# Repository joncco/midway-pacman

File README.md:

This is a reproduction of the PAC-MAN Main Logic board used in Midway's Pac-Man arcade machine.

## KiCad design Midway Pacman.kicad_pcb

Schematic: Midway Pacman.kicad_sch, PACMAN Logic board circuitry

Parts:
C1: 0.01uF; C_Axial_L3.8mm_D2.6mm_P7.70mm_Horizontal
C2, C3: 470uF 10V ELECT.; CP_Axial_L25.0mm_D10.0mm_P30.00mm_Horizontal
C4: 100pF; C_Axial_D4.3mm_P5.00mm_Vertical
C5: 10uF TANT.; CP_Axial_L25.0mm_D10.0mm_P20.00mm_Horizontal
C6: 0.1uF CER.; C_Axial_L3.8mm_D2.6mm_P10.00mm_Horizontal
C7, C8: 10000uF 10V ELECT. AX.; CP_Axial_L25.0mm_D10.0mm_P48.76mm_Horizontal
C10: 10uF 18V TANT.; CP_Axial_L25.0mm_D10.0mm_P20.00mm_Horizontal
C12, C13, C14, C15, C16, C17, C18, C19, C20, C21, C22, C23, C24, C25, C26: .1uF CER.; C_Axial_D4.3mm_P7.6mm_P10.2mm_dual
C29: 2200uF 25V ELECT.; CP_Axial_L25.0mm_D10.0mm_P48.2mm_Horizontal
C34: 220pF; C_Axial_D4.3mm_P5.00mm_Vertical
C46: 0.1uF; C_Axial_L10.0mm_D4.5mm_P11.50mm_Horizontal
C47: 22pF CER; C_Axial_L10.0mm_D4.5mm_P11.50mm_Horizontal
C48: 4.7uF ELECT. 10v; CP_Axial_D4.3mm_P7.6mm_P18mm_dual
C49: 0.47uF TANT.; C_Oval_L4.6mm_W2.0mm_P2.80mm_MKS02_FKP02
C50: 0.0047uF 100V MYLAR; C_Oval_L4.6mm_W2.0mm_P2.50mm_MKS02_FKP02
C51: 330uF 10V ELECT.; CP_Axial_L25.0mm_D10.0mm_P35.5mm_Horizontal
CP1, CP2, CP3, CP4, CP5, CP6, CP7, CP9, CP10, CP11, CP13, CP14, CP15, CP16, CP17, CP18, CP19, CP20, CP21, CP22, CP23, CP24: 0.1uF; C_Axial_D4.3mm_P7.6mm_P10mm_dual
CP8, CP12, CP25: 0.1uF; C_Axial_D4.3mm_P7.6mm
D1, D2: 1N914B; D_DO-35_SOD27_P11.5mm_Horizontal
D3, D4, D6: 1N4004; D_DO-41_SOD81_P12.753mm_Horizontal
D7, D8: A15; D_DO-41_SOD81_P17.6mm_Horizontal
D9: 1N4735; D_DO-41_SOD81_P12.753mm_Horizontal
H1, H2, H3, H4: MountingHole; MountingHole_3mm
H5, H6, H7, H8, H9, H10: MountingHole; MountingHole_4mm
IR1: 78GU1C; TO-220-4_Vertical
J1: Factory TEST Connector; PAC-MAN_CPU_EDGE
J2: Conn_02x22_Namco_PM; PACMAN-EDGE-CONNECTOR
JP1, JP2, JP5, JP8: SolderJumper_2_Bridged; SolderJumper-2_P1.3mm_Bridged_RoundedPad1.0x1.5mm
JP3, JP4, JP6, JP7: SolderJumper_2_Open; SolderJumper-2_P1.3mm_Open_RoundedPad1.0x1.5mm
Q1: 2N3391A; TO-92
Q3: D40K1; TO-220-3_Vertical
Q6: D44VM4; TO-220-3_Horizontal_TabDown
R1, R5: 22K; R_Axial_DIN0207_L6.3mm_D2.5mm_P10mm_Horizontal
R2: 10K; R_Axial_DIN0207_L6.3mm_D2.5mm_P10mm_Horizontal
R3: 47K; R_Axial_DIN0207_L6.3mm_D2.5mm_P10mm_Horizontal
R4: 100K; R_Axial_DIN0207_L6.3mm_D2.5mm_P10mm_Horizontal
R6: 4.7K; R_Axial_DIN0207_L6.3mm_D2.5mm_P10mm_Horizontal
R7: 2.2K; R_Axial_DIN0207_L6.3mm_D2.5mm_P10mm_Horizontal
R8, R10, R11, R12, R14, R18, R19, R35, R54, R55, R57, R58, R59: 1K; R_Axial_DIN0207_L6.3mm_D2.5mm_P10mm_Horizontal
R9, R15, R17, R34: 470; R_Axial_DIN0207_L6.3mm_D2.5mm_P10mm_Horizontal
R13, R16, R20, R33, R37, R38, R39, R40, R41, R42, R43, R44, R45, R46, R47, R48, R49, R50, R51: 220; R_Axial_DIN0207_L6.3mm_D2.5mm_P10mm_Horizontal
R21, R22, R23: 330; R_Axial_DIN0207_L6.3mm_D2.5mm_P10mm_Horizontal
R28, R29: 10K; R_Axial_DIN0207_L6.3mm_D2.5mm_P11.5mm_Horizontal
R30, R31, R32: 1K; R_Axial_DIN0207_L6.3mm_D2.5mm_P11.5mm_Horizontal
R36: 100; R_Axial_DIN0207_L6.3mm_D2.5mm_P10mm_Horizontal
R52: 50R 5W; R_Axial_Power_L25.0mm_W9.0mm_P27.94mm
R53: 4R 10W; R_Axial_Power_L50.0mm_W9.0mm_P60.96mm
R56: 1K; R_Axial_DIN0207_L6.3mm_D2.5mm_P10.4mm_Horizontal
R91: 10K; Potentiometer_ACP_CA14-H4_Horizontal
R92, R93, R95: 100K; R_Axial_DIN0207_L6.3mm_D2.5mm_P11.5mm_Horizontal
R94: 2K; R_Axial_DIN0207_L6.3mm_D2.5mm_P11.5mm_Horizontal
R96: 22K; R_Axial_DIN0207_L6.3mm_D2.5mm_P11.5mm_Horizontal
RM1, RM2, RM5: 1K x 5p; R_Array_SIP6
RM3, RM4, RM6, RM7, RM8: 1K x 8 OR 1K x 9; R_Array_SIP10
SW1: SW_Push; SW_Push_2P1T_Toggle_CK_PVA1xxH1xxxxxxV2
UA1: 27LS00; DIP-16_W7.62mm_square; not fitted
UA2: 8125; DIP-16_W7.62mm_square
UA3: 74LS158; DIP-16_W7.62mm_square
UA4: 5623; DIP-16_W7.62mm_square
UA5: 74LS157; DIP-16_W7.62mm_square
UA8: 74LS107; DIP-14_W7.62mm_square
UA11: LM1877; DIP-14_W7.62mm_LongPads
UB1: 27LS00; DIP-16_W7.62mm_square; not fitted
UB2: 8125; DIP-16_W7.62mm_square
UB3: 74LS157; DIP-16_W7.62mm_square
UB4: 74LS377; DIP-20_W7.62mm_square
UB5: 74LS194; DIP-16_W7.62mm_square
UB6: Z80CPU; DIP-40_W15.24mm
UB8: 74LS368; DIP-16_W7.62mm_square
UC1: 27LS00; DIP-16_W7.62mm_square; not fitted
UC2: 8125; DIP-16_W7.62mm_square
UC3: 74LS375; DIP-16_W7.62mm_square; not fitted
UC4: 74LS00; DIP-14_W7.62mm_square
UC5: 74LS194; DIP-16_W7.62mm_square
UC8: 74LS74; DIP-14_W7.62mm_square
UC9: 74LS161; DIP-16_W7.62mm_square
UD1: 27LS00; DIP-16_W7.62mm_square; not fitted
UD2: 8125; DIP-16_W7.62mm_square
UD3: 74LS75; DIP-16_W7.62mm_square
UD4: 74LS273; DIP-20_W7.62mm_square
UD6: 285; DIP-28_W15.24mm_square
UD8: 74LS367; DIP-16_W7.62mm_square
UD9: 8 POS DIP SW; DIP-16_W7.62mm_square
UE1, UE2: 74LS161/3; DIP-16_W7.62mm_square
UE3: 74LS20; DIP-14_W7.62mm_square
UE4: 74LS157; DIP-16_W7.62mm_square
UE5: 2716; DIP-24_W15.24mm
UE6: ROM; DIP-24_W15.24mm
UE8: 74LS367; DIP-16_W7.62mm_square
UF1, UF2: 74LS283; DIP-16_W7.62mm_square
UF3: 74LS89; DIP-16_W7.62mm_square
UF4: 74LS86; DIP-14_W7.62mm_square
UF5: 2716; DIP-24_W15.24mm
UF6: ROM; DIP-24_W15.24mm
UF7: 7603; DIP-16_W7.62mm_square
UF8: 74LS367; DIP-16_W7.62mm_square
UH1: 74LS174; DIP-16_W7.62mm_square
UH2: 74LS86; DIP-14_W7.62mm_square
UH3: 74LS89; DIP-16_W7.62mm_square
UH4, UH41: 8T245; DIP-20_W7.62mm_square
UH5: 2716; DIP-24_W15.24mm; not fitted
UH6: ROM; DIP-24_W15.24mm
UH7: 74LS08; DIP-14_W7.62mm_square
UH8: 74LS367; DIP-16_W7.62mm_square
UJ5: 2716; DIP-24_W15.24mm; not fitted
UJ6: ROM; DIP-24_W15.24mm
UJ7: 74LS138; DIP-16_W7.62mm_square
UK1: 74LS283; DIP-16_W7.62mm_square
UK2: 74LS89; DIP-16_W7.62mm_square
UK3: 74LS158; DIP-16_W7.62mm_square
UK4: 2114-2; DIP-18_W7.62mm_square
UK6: ROM; DIP-24_W15.24mm; not fitted
UK7: 4099; DIP-16_W7.62mm_square
UK8: 74LS259; DIP-16_W7.62mm_square
UL1: 74LS174; DIP-16_W7.62mm_square
UL2: 74LS89; DIP-16_W7.62mm_square
UL3: 74LS157; DIP-16_W7.62mm_square
UL4: 2114-2; DIP-18_W7.62mm_square
UL5: 74LS139; DIP-16_W7.62mm_square
UL7: 74LS02; DIP-14_W7.62mm_square
UM1: MB7052; DIP-16_W7.62mm_square
UM2: 74LS273; DIP-20_W7.62mm_square
UM3: MB7057; DIP-16_W7.62mm_square
UM4: 2114-2; DIP-18_W7.62mm_square
UM5: 74LS74; DIP-14_W7.62mm_square
UM6: ROM; DIP-24_W15.24mm; not fitted
UM7: 74LS139; DIP-16_W7.62mm_square
UN1: 4066; DIP-14_W7.62mm_square
UN3: 74LS74; DIP-14_W7.62mm_square
UN4: 2114-2; DIP-18_W7.62mm_square
UN5: 74LS08; DIP-14_W7.62mm_square
UN6: ROM; DIP-24_W15.24mm; not fitted
UN7: 74LS42; DIP-16_W7.62mm_square
UP2: 74LS02; DIP-14_W7.62mm_square
UP3: 74LS10; DIP-14_W7.62mm_square
UP4: 2114-2; DIP-18_W7.62mm_square
UP6: ROM; DIP-24_W15.24mm; not fitted
UP7: DIP_16_Breadboard; DIP-16_W7.62mm_bread_square; not fitted
UR1, UR7: DIP_16_Breadboard; DIP-16_W7.62mm_bread_square; not fitted
UR2, UR3: 74LS161/3; DIP-16_W7.62mm_square
UR4: 2114-2; DIP-18_W7.62mm_square
UR6: 74LS367; DIP-16_W7.62mm_square
US1, US4, US7: DIP_16_Breadboard; DIP-16_W7.62mm_bread_square; not fitted
US2, US3: 74LS161/3; DIP-16_W7.62mm_square
US5: 284; DIP-28_W15.24mm_square
US6: 74LS367; DIP-16_W7.62mm_square
X0: 18.432 MHz; Crystal_HC18-U_Horizontal_1EP_style1

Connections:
3: D8.2 (A), J2.3, J2.C (Pin_25)
4: D7.2 (A), J2.4, J2.D (Pin_26)
5: C7.1, C8.1, C10.1, D6.1 (K), D7.1 (K), D8.1 (K), J2.5, J2.E (Pin_27), Q6.2 (C), R53.2
6: J1.35, J2.6, UB6.26 (~RESET), UK8.15 (Clr), UL7.13
7: D6.2 (A), J2.7, Q3.3 (C)
8: J2.8, R51.1, RM8.3 (R2)
9: J2.9, R49.1, RM8.5 (R4)
10: J2.10, R43.1, RM7.3 (R2)
11: J2.11, R48.1, RM8.6 (R5)
12: J2.12, R41.1, RM7.5 (R4)
13: J2.13, R40.1, RM7.6 (R5)
14: J2.14, R45.1, RM8.9 (R8)
16: J2.16, R13.1, R14.1, R15.1
17: J2.17, R36.1
19: D3.2 (A), J2.19, J2.W (Pin_41)
20: D4.2 (A), J2.20, J2.X (Pin_42)
+16V: C29.1, C49.1, D3.1 (K), D4.1 (K), R52.2, UA11.14 (V+)
/1H: UB8.4, UC8.5 (Q), UD6.2 (1H), UH7.1, UM3.5 (A0), UN5.9, UP3.3, UR3.7, UR3.10 (T)
/1V: UF1.5 (A1), UM5.9 (Q), UR2.7, UR2.10 (T)
/2H: UD6.3 (2H), UF4.10, UH7.2, UL5.2 (A0), UM3.6 (A1), UN5.5, UN5.10, UP3.4, UR3.14 (Q0), UR6.1 (OEa), UR6.15 (OEb), US5.1 (2H), US6.1 (OEa), US6.15 (OEb)
/2V: UF1.3 (A2), UR2.14 (Q0)
/4H: UD4.11 (Cp), UF4.4, UH1.9 (Cp), UL3.13 (I1d), UM3.7 (A2), UP3.5, UR3.13 (Q1), US5.2 (4H)
/4V: UF1.14 (A3), UR2.13 (Q1)
/6M*: UB8.3, UC3.4 (E01), UC3.12 (E23), UD3.4 (E23), UD3.13 (E01), UD6.1 (6M*), UF4.12
/6_MHZ: UA1.12 (WE), UA2.14 (WE), UB1.12 (WE), UB2.14 (WE), UB4.11 (CP), UB5.11 (Cp), UB8.13, UC1.12 (WE), UC2.14 (WE), UC5.11 (Cp), UC8.3 (C), UD1.12 (WE), UD2.14 (WE), UE1.2 (CK), UE2.2 (CK), UR3.2 (CK), US3.2 (CK)
/8H: UE4.13 (I1d), UL3.10 (I1c), UM3.4 (A3), UP2.5, UR3.12 (Q2), US5.3 (8H)
/8V: UF1.12 (A4), UR2.12 (Q2), US5.9 (8V)
/16H: UL3.6 (I1b), UM3.3 (A4), UN3.3 (C), UN3.11 (C), UR3.11 (Q3), US5.4 (16H)
/16V: UF2.5 (A1), UM5.3 (C), UR2.11 (Q3), US5.10 (16V)
/32H: UL3.3 (I1a), UM3.2 (A5), UP3.1, US3.14 (Q0), US5.5 (32H)
/32V: UF2.3 (A2), UP3.11, US2.14 (Q0), US5.11 (32V)
/64H: UN3.12 (D), UP3.2, UP3.13, US3.13 (Q1), US5.6 (64H)
/64V: UF2.14 (A3), UP3.10, US2.13 (Q1), US5.12 (64V)
/128H: US3.12 (Q2), US5.7 (128H)
/128V: UF2.12 (A4), UP3.9, US2.12 (Q2), US5.13 (128V)
/256H: UN3.1 (~R), UN5.1, UP2.1
/A0: J1.27, UB6.30 (A0), UE6.8 (A0), UF6.8 (A0), UH6.8 (A0), UJ6.8 (A0), UK6.8 (A0), UM6.8 (A0), UN6.8 (A0), UP6.8 (A0), US6.12 (I5)
/A1: J1.25, UB6.31 (A1), UE6.7 (A1), UF6.7 (A1), UH6.7 (A1), UJ6.7 (A1), UK6.7 (A1), UM6.7 (A1), UN6.7 (A1), UP6.7 (A1), US6.14 (I6)
/A2: J1.23, UB6.32 (A2), UE6.6 (A2), UF6.6 (A2), UH6.6 (A2), UJ6.6 (A2), UK6.6 (A2), UM6.6 (A2), UN6.6 (A2), UP6.6 (A2), US6.2 (I1)
/A3: J1.21, UB6.33 (A3), UE6.5 (A3), UF6.5 (A3), UH6.5 (A3), UJ6.5 (A3), UK6.5 (A3), UM6.5 (A3), UN6.5 (A3), UP6.5 (A3), US6.6 (I3)
/A4: J1.19, UB6.34 (A4), UE6.4 (A4), UF6.4 (A4), UH6.4 (A4), UJ6.4 (A4), UK6.4 (A4), UM6.4 (A4), UN6.4 (A4), UP6.4 (A4), US6.10 (I4)
/A5: J1.17, UB6.35 (A5), UE6.3 (A5), UF6.3 (A5), UH6.3 (A5), UJ6.3 (A5), UK6.3 (A5), UM6.3 (A5), UN6.3 (A5), UP6.3 (A5), US6.4 (I2)
/A6: J1.15, UB6.36 (A6), UE6.2 (A6), UF6.2 (A6), UH6.2 (A6), UJ6.2 (A6), UK6.2 (A6), UM6.2 (A6), UN6.2 (A6), UP6.2 (A6), UR6.12 (I5)
/A7: J1.13, UB6.37 (A7), UE6.1 (A7), UF6.1 (A7), UH6.1 (A7), UJ6.1 (A7), UK6.1 (A7), UM6.1 (A7), UN6.1 (A7), UP6.1 (A7), UR6.14 (I6)
/A8: J1.11, UB6.38 (A8), UE6.23 (A8), UF6.23 (A8), UH6.23 (A8), UJ6.23 (A8), UK6.23 (A8), UM6.23 (A8), UN6.23 (A8), UP6.23 (A8), UR6.6 (I3)
/A9: J1.9, UB6.39 (A9), UE6.22 (A9), UF6.22 (A9), UH6.22 (A9), UJ6.22 (A9), UK6.22 (A9), UM6.22 (A9), UN6.22 (A9), UP6.22 (A9), UR6.4 (I2)
/A10: J1.7, UB6.40 (A10), UE6.19 (A10), UF6.19 (A10), UH6.19 (A10), UJ6.19 (A10), UK6.19 (A10), UM6.19 (A10), UN6.19 (A10), UP6.19 (A10), UR6.2 (I1)
/A11: J1.8, UB6.1 (A11), UE6.18 (~CE), UF6.18 (~CE), UH6.18 (~CE), UJ6.18 (~CE), UL7.9, UR6.10 (I4)
/A12: J1.10, UB6.2 (A12), UJ7.6 (E3), UL7.6, UN7.15 (A0)
/A13: J1.12, UB6.3 (A13), UN7.14 (A1)
/A14: J1.14, UB6.4 (A14), UM7.2 (A0)
/A15: J1.16, UB6.5 (A15)
/AB0: UF3.1 (A0), UH3.1 (A0), UK4.15 (A9), UK7.5 (A0), UK8.1 (A0), UL3.14 (I0d), UL4.15 (A9), UM4.15 (A9), UN4.15 (A9), UP4.15 (A9), UR4.15 (A9), US5.26 (AB0), US6.11 (O5b)
/AB1: UF3.15 (A1), UH3.15 (A1), UK4.16 (A8), UK7.6 (A1), UK8.2 (A1), UL3.11 (I0c), UL4.16 (A8), UM4.16 (A8), UN4.16 (A8), UP4.16 (A8), UR4.16 (A8), US5.25 (AB1), US6.13 (O6b)
/AB2: UF3.14 (A2), UH3.14 (A2), UK4.17 (A7), UK7.7 (A2), UK8.3 (A2), UL3.5 (I0b), UL4.17 (A7), UM4.17 (A7), UN4.17 (A7), UP4.17 (A7), UR4.17 (A7), US5.24 (AB2), US6.3 (O1a)
/AB3: UF3.13 (A3), UH3.13 (A3), UK4.1 (A6), UL3.2 (I0a), UL4.1 (A6), UM4.1 (A6), UN4.1 (A6), UP4.1 (A6), UR4.1 (A6), US5.23 (AB3), US6.7 (O3a)
/AB4: UK4.2 (A5), UL4.2 (A5), UM4.2 (A5), UM7.14 (A0), UN4.2 (A5), UP4.2 (A5), UR4.2 (A5), US5.22 (AB4), US6.9 (O4a)
/AB5: UK4.3 (A4), UL4.3 (A4), UM4.3 (A4), UM7.13 (A1), UN4.3 (A4), UP4.3 (A4), UR4.3 (A4), US5.21 (AB5), US6.5 (O2a)
/AB6: UJ7.1 (A0), UK4.4 (A3), UL4.4 (A3), UM4.4 (A3), UN4.4 (A3), UP4.4 (A3), UR4.4 (A3), UR6.11 (O5b), US5.20 (AB6)
/AB7: UJ7.2 (A1), UK4.7 (A2), UL4.7 (A2), UM4.7 (A2), UN4.7 (A2), UP4.7 (A2), UR4.7 (A2), UR6.13 (O6b), US5.19 (AB7)
/AB8: UK4.6 (A1), UL4.6 (A1), UM4.6 (A1), UN4.6 (A1), UP4.6 (A1), UR4.6 (A1), UR6.7 (O3a), US5.18 (AB8)
/AB9: UK4.5 (A0), UL4.5 (A0), UM4.5 (A0), UN4.5 (A0), UP4.5 (A0), UR4.5 (A0), UR6.5 (O2a), US5.17 (AB9)
/AB10: UL5.14 (A0), UR6.3 (O1a), US5.16 (AB10)
/AB11: UL5.13 (A1), UR6.9 (O4a), US5.15 (AB11)
/CA0: UE5.8 (A0), UF5.8 (A0), UH2.8, UH5.8 (A0), UJ5.8 (A0)
/CA1: UE5.7 (A1), UF5.7 (A1), UH2.11, UH5.7 (A1), UJ5.7 (A1)
/CA2: UE5.6 (A2), UF5.6 (A2), UH2.3, UH5.6 (A2), UJ5.6 (A2)
/CA3: UE5.5 (A3), UF4.6, UF5.5 (A3), UH5.5 (A3), UJ5.5 (A3)
/CA4: UE4.12 (Zd), UE5.4 (A4), UF5.4 (A4), UH5.4 (A4), UJ5.4 (A4)
/CA5: UE4.7 (Zb), UE5.3 (A5), UF5.3 (A5), UH5.3 (A5), UJ5.3 (A5)
/CA6: UD4.15 (Q5), UE5.2 (A6), UF5.2 (A6), UH5.2 (A6), UJ5.2 (A6)
/CA7: UD4.12 (Q4), UE5.1 (A7), UF5.1 (A7), UH5.1 (A7), UJ5.1 (A7)
/CA8: UD4.9 (Q3), UE5.23 (A8), UF5.23 (A8), UH5.23 (A8), UJ5.23 (A8)
/CA9: UD4.6 (Q2), UE5.22 (A9), UF5.22 (A9), UH5.22 (A9), UJ5.22 (A9)
/CA10: UD4.5 (Q1), UE5.19 (A10), UF5.19 (A10), UH5.19 (A10), UJ5.19 (A10)
/CD0: UC5.6 (D), UE5.9 (D0), UF5.9 (D0), UH5.9 (D0), UJ5.9 (D0)
/CD1: UC5.5 (C), UE5.10 (D1), UF5.10 (D1), UH5.10 (D1), UJ5.10 (D1)
/CD2: UC5.4 (B), UE5.11 (D2), UF5.11 (D2), UH5.11 (D2), UJ5.11 (D2)
/CD3: UC5.3 (A), UE5.13 (D3), UF5.13 (D3), UH5.13 (D3), UJ5.13 (D3)
/CD4: UB5.6 (D), UE5.14 (D4), UF5.14 (D4), UH5.14 (D4), UJ5.14 (D4)
/CD5: UB5.5 (C), UE5.15 (D5), UF5.15 (D5), UH5.15 (D5), UJ5.15 (D5)
/CD6: UB5.4 (B), UE5.16 (D6), UF5.16 (D6), UH5.16 (D6), UJ5.16 (D6)
/CD7: UB5.3 (A), UE5.17 (D7), UF5.17 (D7), UH5.17 (D7), UJ5.17 (D7)
/D0: J1.34, UB6.14 (D0), UD6.19 (D0), UE6.9 (D0), UF6.9 (D0), UH6.9 (D0), UJ6.9 (D0), UK6.9 (D0), UM6.9 (D0), UN6.9 (D0), UP6.9 (D0)
/D1: J1.36, UB6.15 (D1), UD6.18 (D1), UE6.10 (D1), UF6.10 (D1), UH6.10 (D1), UJ6.10 (D1), UK6.10 (D1), UM6.10 (D1), UN6.10 (D1), UP6.10 (D1)
/D2: J1.30, UB6.12 (D2), UD6.21 (D2), UE6.11 (D2), UF6.11 (D2), UH6.11 (D2), UJ6.11 (D2), UK6.11 (D2), UM6.11 (D2), UN6.11 (D2), UP6.11 (D2)
/D3: J1.22, UB6.8 (D3), UD6.24 (D3), UE6.13 (D3), UF6.13 (D3), UH6.13 (D3), UJ6.13 (D3), UK6.13 (D3), UM6.13 (D3), UN6.13 (D3), UP6.13 (D3)
/D4: J1.20, UB6.7 (D4), UD6.25 (D4), UE6.14 (D4), UF6.14 (D4), UH6.14 (D4), UJ6.14 (D4), UK6.14 (D4), UM6.14 (D4), UN6.14 (D4), UP6.14 (D4)
/D5: J1.24, UB6.9 (D5), UD6.23 (D5), UE6.15 (D5), UF6.15 (D5), UH6.15 (D5), UJ6.15 (D5), UK6.15 (D5), UM6.15 (D5), UN6.15 (D5), UP6.15 (D5)
/D6: J1.26, UB6.10 (D6), UD6.22 (D6), UE6.16 (D6), UF6.16 (D6), UH6.16 (D6), UJ6.16 (D6), UK6.16 (D6), UM6.16 (D6), UN6.16 (D6), UP6.16 (D6)
/D7: J1.32, UB6.13 (D7), UD6.20 (D7), UE6.17 (D7), UF6.17 (D7), UH6.17 (D7), UJ6.17 (D7), UK6.17 (D7), UM6.17 (D7), UN6.17 (D7), UP6.17 (D7)
/DB0: UB4.18 (D7), UD4.18 (D7), UD6.10 (DB0), UE8.9 (O4a), UF8.9 (O4a), UF8.11 (O5b), UH3.4 (Di0), UH4.11 (B7), UH41.12 (B7), UK3.14 (I0c), UK7.3 (D), UK8.13 (D)
/DB1: UB4.17 (D6), UD4.17 (D6), UD6.11 (DB1), UE8.5 (O2a), UF8.5 (O2a), UF8.13 (O6b), UH3.6 (DI1), UH4.12 (B6), UH41.13 (B6), UK3.11 (I0d)
/DB2: UB4.14 (D5), UD4.14 (D5), UD6.8 (DB2), UD8.7 (O3a), UE8.7 (O3a), UF8.7 (O3a), UH3.10 (DI2), UH4.13 (B5), UH41.14 (B5), UK3.5 (I0b)
/DB3: UB4.13 (D4), UD4.13 (D4), UD6.5 (DB3), UD8.11 (O5b), UE8.13 (O6b), UF8.3 (O1a), UH3.12 (DI3), UH4.14 (B4), UH41.15 (B4), UK3.2 (I0a)
/DB4: UB4.8 (D3), UD4.8 (D3), UD6.4 (DB4), UD8.3 (O1a), UE8.3 (O1a), UF3.4 (Di0), UH4.15 (B3), UH8.3 (O1a), UH41.16 (B3)
/DB5: UD4.7 (D2), UD6.6 (DB5), UD8.5 (O2a), UE8.11 (O5b), UF3.6 (DI1), UH4.16 (B2), UH8.7 (O3a), UH41.17 (B2)
/DB6: UD4.4 (D1), UD6.7 (DB6), UD8.9 (O4a), UF3.10 (DI2), UH4.17 (B1), UH8.9 (O4a), UH8.11 (O5b), UH41.18 (B1)
/DB7: UD4.3 (D0), UD6.9 (DB7), UD8.13 (O6b), UF3.12 (DI3), UH4.18 (B0), UH8.5 (O2a), UH8.13 (O6b), UH41.19 (B0)
/DR0: RM4.4 (R3), UE1.3 (D0), UF1.6 (B1), UH3.5 (~DO0)
/DR1: RM4.3 (R2), UE1.4 (D1), UF1.2 (B2), UH3.7 (~DO1)
/DR2: RM4.2 (R1), UE1.5 (D2), UF1.15 (B3), UH3.9 (~DO2)
/DR3: RM4.5 (R4), UE1.6 (D3), UF1.11 (B4), UH3.11 (~DO3)
/DR4: RM4.6 (R5), UE2.3 (D0), UF2.6 (B1), UF3.5 (~DO0)
/DR5: RM4.8 (R7), UE2.4 (D1), UF2.2 (B2), UF3.7 (~DO1)
/DR6: RM4.9 (R8), UE2.5 (D2), UF2.15 (B3), UF3.9 (~DO2)
/DR7: RM4.7 (R6), UE2.6 (D3), UF2.11 (B4), UF3.11 (~DO3)
/DVR0: UH4.9 (A7), UH41.8 (A7), UK4.11 (D3), UL4.11 (D3), UM4.11 (D3)
/DVR1: UH4.8 (A6), UH41.7 (A6), UK4.12 (D2), UL4.12 (D2), UM4.12 (D2)
/DVR2: UH4.7 (A5), UH41.6 (A5), UK4.13 (D1), UL4.13 (D1), UM4.13 (D1)
/DVR3: UH4.6 (A4), UH41.5 (A4), UK4.14 (D0), UL4.14 (D0), UM4.14 (D0)
/DVR4: UH4.5 (A3), UH41.4 (A3), UN4.11 (D3), UP4.11 (D3), UR4.11 (D3)
/DVR5: UH4.4 (A2), UH41.3 (A2), UN4.12 (D2), UP4.12 (D2), UR4.12 (D2)
/DVR6: UH4.3 (A1), UH41.2 (A1), UN4.13 (D1), UP4.13 (D1), UR4.13 (D1)
/DVR7: UH4.2 (A0), UH41.1 (A0), UN4.14 (D0), UP4.14 (D0), UR4.14 (D0)
/FLIP: UE4.2 (I0a), UE4.11 (I0c), UH7.11, US5.27
/H SYNC: UM5.11 (C), UN3.8 (~Q), UR2.2 (CK), US2.2 (CK)
/H_BLANK: UH1.4 (D1), UN3.5 (Q), UN3.10 (~S)
/IRQ_ON: UC8.10 (~S), UH7.8
/O31: J1.31, UB6.28 (~RFSH), UM7.3 (A1)
/O43: J1.43, UB6.22 (~WR)
/O44: J1.44, UB6.19 (~MREQ), UM7.1 (E)
/RA0: UA1.1 (A1), UA2.4 (A1), UB1.1 (A1), UB2.4 (A1), UC1.1 (A1), UC2.4 (A1), UD1.1 (A1), UD2.4 (A1), UE1.14 (Q0)
/RA1: UA1.2 (A0), UA2.3 (A0), UB1.2 (A0), UB2.3 (A0), UC1.2 (A0), UC2.3 (A0), UD1.2 (A0), UD2.3 (A0), UE1.13 (Q1)
/RA2: UA1.7 (A4), UA2.2 (A4), UB1.7 (A4), UB2.2 (A4), UC1.7 (A4), UC2.2 (A4), UD1.7 (A4), UD2.2 (A4), UE1.12 (Q2)
/RA3: UA1.9 (A5), UA2.13 (A5), UB1.9 (A5), UB2.13 (A5), UC1.9 (A5), UC2.13 (A5), UD1.9 (A5), UD2.13 (A5), UE1.11 (Q3)
/RA4: UA1.10 (A6), UA2.12 (A6), UB1.10 (A6), UB2.12 (A6), UC1.10 (A6), UC2.12 (A6), UD1.10 (A6), UD2.12 (A6), UE2.14 (Q0)
/RA5: UA1.11 (A7), UA2.11 (A7), UB1.11 (A7), UB2.11 (A7), UC1.11 (A7), UC2.11 (A7), UD1.11 (A7), UD2.11 (A7), UE2.13 (Q1)
/RA6: UA1.14 (A3), UA2.10 (A3), UB1.14 (A3), UB2.10 (A3), UC1.14 (A3), UC2.10 (A3), UD1.14 (A3), UD2.10 (A3), UE2.12 (Q2)
/RA7: UA1.15 (A2), UA2.9 (A2), UB1.15 (A2), UB2.9 (A2), UC1.15 (A2), UC2.9 (A2), UD1.15 (A2), UD2.9 (A2), UE2.11 (Q3)
/R/W: UD6.13 (R/~W), UH4.1 (A->B), UH41.11 (CE), UJ7.3 (A2), UK4.10 (~WE), UL4.10 (~WE), UM4.10 (~WE), UN4.10 (~WE), UP4.10 (~WE), UR4.10 (~WE)
/SOUND: C1.1, R1.2, R2.2, R3.2, R4.2, R5.2, R96.2
/SOUND_ON: UM2.1 (~Mr)
/VBLANK: UC8.11 (C), UC9.2 (CP), UM5.6 (~Q)
/~6M*: UF4.11, UM3.13 (~CS)
/~256H: UP2.2, UP2.3, US3.11 (Q3), US5.8 (~256H)
/~BUSACK: J1.41, UB6.23 (~BUSACK)
/~BUSRQ: J1.37, R12.1, UB6.25 (~BUSRQ)
/~CLK: J1.18, R20.1, UB6.6 (~CLK), UB8.5
/~CMPSYNC: R35.1, R36.2, UN5.11
/~CNTR_LD: UC4.8, UE1.9 (~PE), UE2.9 (~PE)
/~DIP_SW: UD8.1 (OEa), UD8.15 (OEb), UF8.15 (OEb), UJ7.9 (O6)
/~HALT: J1.42, UB6.18 (~HALT)
/~H_BLANK: UB4.7 (D2), UN3.6 (~Q), UN5.4
/~IN0: UE8.1 (OEa), UE8.15 (OEb), UH8.15 (OEb), UJ7.11 (O4)
/~IN1: UF8.1 (OEa), UH8.1 (OEa), UJ7.10 (O5)
/~IORQ: J1.46, UB6.20 (~IORQ), UD6.15 (~IORQ)
/~IRQ: J1.38, UB6.16 (~INT), UC8.9 (Q)
/~M1: J1.33, UB6.27 (~M1), UD6.26 (~M1)
/~NMI: J1.40, R19.1, UB6.17 (~NMI)
/~OBJ_ON: UA1.3 (CS1), UA2.1 (CS), UB1.3 (CS1), UB2.1 (CS), UB4.5 (Q1), UC1.3 (CS1), UC2.1 (CS), UC4.1, UC4.2, UD1.3 (CS1), UD2.1 (CS)
/~OUT: UJ7.15 (O0), UK7.4 (WR), UK8.14 (E)
/~RD: J1.45, UB6.21 (~RD), UD6.16 (~RD), UN7.13 (A2)
/~V SYNC: UN5.12, US2.11 (Q3)
/~VRAM: UH4.19 (CE), UH41.9 (A->B), UL5.15 (E), UL7.1
/~V_BLANK: UC4.13, UM5.5 (Q)
/~WDR: UC9.1 (~MR), UJ7.12 (O3)
/~WR0: UM3.1 (A6), UM7.12 (O0)
/~WREQ: J1.39, UB6.24 (~WAIT), UH7.6
F: J2.F (Pin_28), R95.2, UA11.2
GND: C1.2, C2.2, C3.2, C5.2, C6.2, C7.2, C8.2, C12.2, C13.2, C14.2, C15.2, C16.2, C17.2, C18.2, C19.2, C20.2, C21.2, C22.2, C23.2, C24.2, C25.2, C26.2, C29.2, C34.2, C49.2, C50.2, C51.2, CP1.2, CP2.1, CP3.2, CP4.1, CP5.1, CP6.1, CP7.1, CP8.1, CP9.1, CP10.1, CP11.2, CP12.1, CP13.1, CP14.2, CP15.2, CP16.1, CP17.1, CP18.2, CP19.2, CP20.2, CP21.1, CP22.1, CP23.2, CP24.1, CP25.1, D1.2 (A), D9.2 (A), IR1.4 (COM), J1.1, J1.2, J1.3, J1.4, J1.29, J1.47, J1.48, J1.49, J1.50, J2.1, J2.2, J2.15, J2.21, J2.22, J2.A (Pin_23), J2.B (Pin_24), J2.S (Pin_37), J2.Y (Pin_43), J2.Z (Pin_44), JP1.1 (A), JP3.1 (A), JP5.1 (A), JP6.1 (A), JP7.1 (A), JP8.1 (A), Q1.1 (E), Q3.1 (E), R29.2, R91.3, SW1.1, UA1.4 (CS2), UA1.5 (CS3), UA1.8 (GND), UA2.5 (A), UA2.6 (A), UA2.8 (GND), UA3.8 (GND), UA4.8 (GND), UA4.13 (~CS), UA4.14 (~CS), UA5.8 (GND), UA5.15 (E), UA8.7 (GND), UA11.3 (GND), UA11.4 (GND), UA11.5 (GND), UA11.10 (GND), UA11.11 (GND), UA11.12 (GND), UB1.4 (CS2), UB1.5 (CS3), UB1.8 (GND), UB2.5 (A), UB2.6 (A), UB2.8 (GND), UB3.8 (GND), UB4.10 (GND), UB5.2 (Dsr), UB5.7 (Dsl), UB5.8 (GND), UB6.29 (GND), UB8.1, UB8.8 (GND), UB8.15, UC1.4 (CS2), UC1.5 (CS3), UC1.8 (GND), UC2.5 (A), UC2.6 (A), UC2.8 (GND), UC3.8 (GND), UC4.7 (GND), UC5.2 (Dsr), UC5.7 (Dsl), UC5.8 (GND), UC8.7 (GND), UC8.12 (D), UC9.8 (GND), UD1.4 (CS2), UD1.5 (CS3), UD1.8 (GND), UD2.5 (A), UD2.6 (A), UD2.8 (GND), UD3.12 (GND), UD4.10 (GND), UD6.14 (GND), UD8.8 (GND), UD9.7, UD9.9, UD9.11, UD9.12, UD9.13, UD9.14, UD9.15, UD9.16, UE1.8 (GND), UE2.8 (GND), UE3.7 (GND), UE4.8 (GND), UE4.15 (E), UE5.12 (GND), UE6.12 (GND), UE8.8 (GND), UF1.8 (GND), UF2.8 (GND), UF3.8 (GND), UF4.7 (GND), UF4.9, UF5.12 (GND), UF6.12 (GND), UF7.8 (GND), UF7.15 (~CS), UF8.8 (GND), UH1.8 (GND), UH2.7 (GND), UH3.8 (GND), UH4.10 (GND), UH5.12 (GND), UH6.12 (GND), UH7.7 (GND), UH8.8 (GND), UH41.10 (GND), UJ5.12 (GND), UJ6.12 (GND), UJ7.8 (GND), UK1.8 (GND), UK2.2 (~CE), UK2.8 (GND), UK3.8 (GND), UK3.15 (E), UK4.9 (GND), UK6.12 (GND), UK7.8 (Vss), UK8.8 (GND), UL1.8 (GND), UL2.2 (~CE), UL2.8 (GND), UL3.8 (GND), UL3.15 (E), UL4.9 (GND), UL5.1 (E), UL5.8 (GND), UL7.7 (GND), UL7.8, UL7.11, UM1.8 (GND), UM1.13 (~CS), UM1.14 (~CS), UM2.10 (GND), UM3.8 (GND), UM3.14 (~CS), UM4.9 (GND), UM5.7 (GND), UM6.12 (GND), UM7.8 (GND), UN1.7 (VSS), UN3.7 (GND), UN4.9 (GND), UN5.7 (GND), UN6.12 (GND), UN7.8 (GND), UP2.7 (GND), UP3.7 (GND), UP4.9 (GND), UP6.12 (GND), UP7.8, UP7.24 (Pin_8), UR1.8, UR1.24 (Pin_8), UR2.3 (D0), UR2.4 (D1), UR2.8 (GND), UR3.3 (D0), UR3.4 (D1), UR3.5 (D2), UR3.6 (D3), UR3.8 (GND), UR4.9 (GND), UR6.8 (GND), UR7.8, UR7.24 (Pin_8), US1.8, US1.24 (Pin_8), US2.6 (D3), US2.8 (GND), US3.3 (D0), US3.4 (D1), US3.6 (D3), US3.8 (GND), US4.8, US4.24 (Pin_8), US5.14 (GND), US6.8 (GND), US7.8, US7.24 (Pin_8), X0.3
H: C47.2, J2.H (Pin_29), R93.1, UA11.13
J: J2.J (Pin_30), R50.1, RM8.4 (R3)
K: J2.K (Pin_31), R44.1, RM7.2 (R1)
L: J2.L (Pin_32), R42.1, RM7.4 (R3)
M: J2.M (Pin_33), R47.1, RM8.7 (R6)
N: J2.N (Pin_34), R46.1, RM8.8 (R7)
unnamed: C4.1, R21.1, UB8.6, UB8.11
unnamed: C4.2, R22.1, UB8.10
unnamed: C46.1, R91.2
unnamed: C48.2, R94.1
unnamed: C10.2, D1.1 (K), R28.2
unnamed: D2.2 (A), Q3.2 (B), R23.1
unnamed: D2.1 (K), Q1.2 (C), R30.1, SW1.2, UC9.9 (~PE)
unnamed: C5.1, IR1.3 (IN), R52.1
unnamed: C6.1, IR1.2 (OUT), Q6.1 (B)
unnamed: JP1.2 (B), R11.2, UM3.15 (A7)
unnamed: JP2.1 (A), UE4.1 (S), UH1.5 (Q1)
unnamed: JP2.2 (B), JP3.2 (B), UL5.3 (A1)
unnamed: JP4.1 (A), UA3.15 (E), UB4.6 (Q2), UC4.5, UC4.12
unnamed: JP4.2 (B), JP5.2 (B), R10.1, UA4.15 (A7)
unnamed: JP6.2 (B), RM6.8 (R7), UD8.10 (I4)
unnamed: JP7.2 (B), RM6.9 (R8), UD8.14 (I6)
unnamed: JP8.2 (B), R54.1, UF7.14 (A4)
unnamed: Q1.3 (B), R28.1, R29.1
unnamed: R1.1, UN1.2
unnamed: R2.1, UN1.3
unnamed: R3.1, UN1.10
unnamed: R4.1, UN1.9
unnamed: R6.2, R7.2, R8.2, R9.2, UN1.1, UN1.4, UN1.8, UN1.11
unnamed: R21.2, UB8.12, X0.1
unnamed: R22.2, UB8.9, X0.2
unnamed: R91.1, R96.1
unnamed: RM1.2 (R1), UA3.2 (I0a), UA4.9 (D3), UB3.2 (I0a)
unnamed: RM1.3 (R2), UA3.14 (I0d), UA4.12 (D0), UB3.14 (I0d)
unnamed: RM1.4 (R3), UA3.5 (I0b), UA4.10 (D2), UB3.5 (I0b)
unnamed: RM1.5 (R4), UA3.11 (I0c), UA4.11 (D1), UB3.11 (I0c)
unnamed: RM2.2 (R1), UA1.6 (~DO), UA2.7 (~DO), UC3.1 (D0), UD3.2 (D0)
unnamed: RM2.3 (R2), UC3.15 (D3), UD1.6 (~DO), UD2.7 (~DO), UD3.3 (D1)
unnamed: RM2.4 (R3), UB1.6 (~DO), UB2.7 (~DO), UC3.7 (D1), UD3.7 (D3)
unnamed: RM2.5 (R4), UC1.6 (~DO), UC2.7 (~DO), UC3.9 (D2), UD3.6 (D2)
unnamed: RM3.2 (R1), UK1.15 (B3), UL2.9 (~DO2), UM2.4 (D1)
unnamed: RM3.3 (R2), UK1.2 (B2), UL2.7 (~DO1), UM2.7 (D2)
unnamed: RM3.4 (R3), UK1.14 (A3), UK2.9 (~DO2), UM1.15 (A7)
unnamed: RM3.5 (R4), UK1.3 (A2), UK2.7 (~DO1), UM1.1 (A6)
unnamed: RM3.6 (R5), UK1.12 (A4), UK2.11 (~DO3)
unnamed: RM3.7 (R6), UK1.5 (A1), UK2.5 (~DO0), UM1.2 (A5)
unnamed: RM3.8 (R7), UK1.6 (B1), UL2.5 (~DO0), UM2.8 (D3)
unnamed: RM3.9 (R8), UK1.11 (B4), UL2.11 (~DO3), UM2.3 (D0)
unnamed: RM5.2 (R1), UL1.9 (Cp), UM3.12 (D0)
unnamed: RM5.3 (R2), UK2.3 (WE), UM3.11 (D1)
unnamed: RM5.4 (R3), UM2.11 (Cp), UM3.10 (D2)
unnamed: RM5.5 (R4), UL1.1 (~Mr), UM3.9 (D3)
unnamed: RM6.2 (R1), UD9.1, UF8.12 (I5)
unnamed: RM6.3 (R2), UD9.2, UF8.14 (I6)
unnamed: RM6.4 (R3), UD8.6 (I3), UD9.3
unnamed: RM6.5 (R4), UD8.12 (I5), UD9.4
unnamed: RM6.6 (R5), UD8.2 (I1), UD9.5
unnamed: RM6.7 (R6), UD8.4 (I2), UD9.6
unnamed: RM8.2 (R1), UD9.10, UE8.2 (I1)
unnamed: UA1.13 (DI), UA2.15 (DI), UA3.4 (Za)
unnamed: UA3.3 (I1a), UB3.3 (I1a), UC3.2 (~Q0), UD3.1 (~Q0)
unnamed: UA3.6 (I1b), UB3.6 (I1b), UC3.6 (~Q1), UD3.8 (~Q3)
unnamed: UA3.10 (I1c), UB3.10 (I1c), UC3.10 (~Q2), UD3.11 (~Q2)
unnamed: UA3.13 (I1d), UB3.13 (I1d), UC3.14 (~Q3), UD3.14 (~Q1)
unnamed: UA3.1 (S), UB3.1 (S), UE3.6
unnamed: UA3.7 (Zb), UB1.13 (DI), UB2.15 (DI)
unnamed: UA3.9 (Zc), UC1.13 (DI), UC2.15 (DI)
unnamed: UA3.12 (Zd), UD1.13 (DI), UD2.15 (DI)
unnamed: UA4.5 (A0), UA5.12 (Zd)
unnamed: UA4.6 (A1), UA5.9 (Zc)
unnamed: UA4.7 (A2), UB4.19 (Q7)
unnamed: UA4.4 (A3), UB4.16 (Q6)
unnamed: UA4.3 (A4), UB4.15 (Q5)
unnamed: UA4.2 (A5), UB4.12 (Q4)
unnamed: UA4.1 (A6), UB4.9 (Q3)
unnamed: UA5.2 (I0a), UA5.6 (I1b), UN5.8
unnamed: UA5.11 (I0c), UB5.15 (Q0)
unnamed: UA5.14 (I0d), UC5.15 (Q0)
unnamed: UA5.10 (I1c), UB5.12 (Q3)
unnamed: UA5.13 (I1d), UC5.12 (Q3)
unnamed: UA5.1 (S), UB4.2 (Q0)
unnamed: UA5.4 (Za), UB5.9 (S0), UC5.9 (S0)
unnamed: UA5.7 (Zb), UB5.10 (S1), UC5.10 (S1)
unnamed: UA8.9 (C), UA8.12 (C), UB8.7
unnamed: UA8.1 (J), UA8.5 (Q)
unnamed: UA8.3 (Q), UB8.14
unnamed: UA8.2 (~Q), UA8.8 (J)
unnamed: UA8.6 (~Q), UB8.2
unnamed: C46.2, R92.1, UA11.6 (+)
unnamed: R94.2, R95.1, UA11.7 (-)
unnamed: C51.1, R92.2, UA11.1 (BIAS), UA11.9 (+)
unnamed: C47.1, C48.1, C50.1, R93.2, UA11.8 (-)
unnamed: UB3.15 (E), UC4.11
unnamed: UB3.4 (Za), UF7.13 (A3)
unnamed: UB3.7 (Zb), UF7.12 (A2)
unnamed: UB3.9 (Zc), UF7.11 (A1)
unnamed: UB3.12 (Zd), UF7.10 (A0)
unnamed: UB4.3 (D0), UE4.9 (Zc), UF4.5
unnamed: UB4.4 (D1), UN5.3
unnamed: UB4.1 (~E), UP2.6, UP3.6
unnamed: UC3.3 (Q0), UD3.16 (Q0), UE3.1
unnamed: UC3.5 (Q1), UD3.9 (Q3), UE3.5
unnamed: UC3.11 (Q2), UD3.10 (Q2), UE3.4
unnamed: UC3.13 (Q3), UD3.15 (Q1), UE3.2
unnamed: UC4.3, UC4.4
unnamed: UC4.6, UC4.9
unnamed: UC4.10, UP2.4
unnamed: UC8.2 (D), UC8.6 (~Q)
unnamed: R31.1, UC9.7 (CEP), UC9.10 (CET), UD9.8, UH7.5
unnamed: UC9.15 (TC), UK7.2 (R), UL7.12
unnamed: UD4.2 (Q0), UE5.18 (~CE), UF4.1, UF5.18 (~CE)
unnamed: UD4.16 (Q6), UE4.3 (I1a), UE4.5 (I0b)
unnamed: UD4.19 (Q7), UE4.10 (I1c), UE4.14 (I0d)
unnamed: UD6.12 (CK), UJ7.4 (E1), UJ7.5 (E2), UL7.5
unnamed: UD6.27 (~CS), UM7.7 (O3)
unnamed: UD6.17 (~WREQ), UH7.4
unnamed: UE1.15 (C), UE2.7, UE2.10 (T)
unnamed: UE4.6 (I1b), UH2.6
unnamed: UE4.4 (Za), UH2.2, UH2.5, UH2.10, UH2.13
unnamed: C22.1, R47.2, UE8.4 (I2)
unnamed: C23.1, R48.2, UE8.6 (I3)
unnamed: C21.1, R46.2, UE8.10 (I4)
unnamed: C25.1, R50.2, UE8.12 (I5)
unnamed: C20.1, R45.2, UE8.14 (I6)
unnamed: UF1.7 (C0), UF3.2 (~CE), UH3.2 (~CE), UN5.6
unnamed: UF1.9 (C4), UF2.7 (C0)
unnamed: UF1.4 (S1), UH1.13 (D4)
unnamed: UF1.1 (S2), UH1.11 (D3)
unnamed: UF1.13 (S3), UH1.6 (D2)
unnamed: UF1.10 (S4), UH1.3 (D0)
unnamed: UE3.9, UF2.4 (S1)
unnamed: UE3.10, UF2.1 (S2)
unnamed: UE3.13, UF2.13 (S3)
unnamed: UE3.12, UF2.10 (S4)
unnamed: UF3.3 (WE), UH3.3 (WE), UM7.10 (O2)
unnamed: UF4.3, UH5.18 (~CE), UJ5.18 (~CE)
unnamed: R18.2, UF7.1 (D0)
unnamed: R17.2, UF7.2 (D1)
unnamed: R16.2, UF7.3 (D2)
unnamed: R14.2, UF7.4 (D3)
unnamed: R15.2, UF7.5 (D4)
unnamed: R13.2, UF7.6 (D5)
unnamed: R34.2, UF7.7 (D6)
unnamed: R33.2, UF7.9 (D7)
unnamed: C12.1, R37.2, UF8.2 (I1)
unnamed: C14.1, R39.2, UF8.4 (I2)
unnamed: C15.1, R40.2, UF8.6 (I3)
unnamed: C16.1, R41.2, UF8.10 (I4)
unnamed: UE3.8, UH1.14 (D5)
unnamed: UH1.2 (Q0), UH2.4
unnamed: UH1.7 (Q2), UH2.1
unnamed: UH1.10 (Q3), UH2.12
unnamed: UH1.12 (Q4), UH2.9
unnamed: UH1.15 (Q5), UN5.2
unnamed: UH7.3, UL7.3
unnamed: C19.1, R44.2, UH8.2 (I1)
unnamed: C13.1, R38.2, UH8.4 (I2)
unnamed: C17.1, R42.2, UH8.6 (I3)
unnamed: C18.1, R43.2, UH8.10 (I4)
unnamed: C26.1, R51.2, UH8.12 (I5)
unnamed: C24.1, R49.2, UH8.14 (I6)
unnamed: UJ7.14 (O1), UM7.15 (E)
unnamed: UK1.7 (C0), UL1.2 (Q0)
unnamed: UK1.9 (C4), UL1.3 (D0)
unnamed: UK1.4 (S1), UL1.13 (D4)
unnamed: UK1.1 (S2), UL1.11 (D3)
unnamed: UK1.13 (S3), UL1.6 (D2)
unnamed: UK1.10 (S4), UL1.4 (D1)
unnamed: UK2.1 (A0), UL2.1 (A0), UL3.12 (Zd)
unnamed: UK2.15 (A1), UL2.15 (A1), UL3.9 (Zc)
unnamed: UK2.14 (A2), UL2.14 (A2), UL3.7 (Zb)
unnamed: UK2.13 (A3), UL2.13 (A3), UL3.4 (Za)
unnamed: UK2.6 (DI1), UK3.9 (Zd), UL2.6 (DI1)
unnamed: UK2.10 (DI2), UK3.7 (Zb), UL2.10 (DI2)
unnamed: UK2.12 (DI3), UK3.4 (Za), UL2.12 (DI3)
unnamed: UK2.4 (Di0), UK3.12 (Zc), UL2.4 (Di0)
unnamed: UK3.3 (I1a), UL1.5 (Q1), UL1.14 (D5), UM1.3 (A4)
unnamed: UK3.6 (I1b), UL1.7 (Q2), UM1.4 (A3)
unnamed: UK3.13 (I1c), UL1.12 (Q4), UM1.6 (A1)
unnamed: UK3.10 (I1d), UL1.10 (Q3), UM1.7 (A2)
unnamed: C34.1, UF4.8, UK3.1 (S), UL3.1 (S)
unnamed: UK4.8 (~CS), UL5.12 (O0), UN4.8 (~CS)
unnamed: UK6.18 (~CE), UL7.10, UM6.18 (~CE), UN6.18 (~CE), UP6.18 (~CE)
unnamed: UH7.9, UH7.10, UK7.9 (Q0), UK8.4 (Q0)
unnamed: UK7.10 (Q1), UK8.5 (Q1)
unnamed: UH7.12, UH7.13, UK7.12 (Q3), UK8.7 (Q3)
unnamed: UK7.13 (Q4), UK8.9 (Q4)
unnamed: R23.2, UK7.1 (Q7), UK8.12 (Q7)
unnamed: UL1.15 (Q5), UM1.5 (A0)
unnamed: UL2.3 (WE), UM7.11 (O1)
unnamed: UL4.8 (~CS), UL5.11 (O1), UP4.8 (~CS)
unnamed: UE5.20 (~CE), UH5.20 (~CE), UL5.5 (O1)
unnamed: UF5.20 (~CE), UJ5.20 (~CE), UL5.7 (O3)
unnamed: UL5.9 (O3), UM4.8 (~CS), UR4.8 (~CS)
unnamed: UL7.2, UL7.4
unnamed: UM1.12 (D0), UM2.18 (D7)
unnamed: UM1.11 (D1), UM2.17 (D6)
unnamed: UM1.10 (D2), UM2.14 (D5)
unnamed: UM1.9 (D3), UM2.13 (D4)
unnamed: UM2.2 (Q0), UN1.5
unnamed: UM2.5 (Q1), UN1.13
unnamed: UM2.6 (Q2), UN1.12
unnamed: UM2.9 (Q3), UN1.6
unnamed: R9.1, UM2.12 (Q4)
unnamed: R8.1, UM2.15 (Q5)
unnamed: R7.1, UM2.16 (Q6)
unnamed: R6.1, UM2.19 (Q7)
unnamed: UM5.2 (D), UP3.8
unnamed: UM5.8 (~Q), UM5.12 (D)
unnamed: UM7.6 (O2), UN7.12 (A3)
unnamed: UN3.2 (D), UP3.12
unnamed: UN3.9 (Q), UN5.13
unnamed: UE6.20 (~CE), UK6.20 (~CE), UN7.1 (0)
unnamed: UF6.20 (~CE), UM6.20 (~CE), UN7.2 (1)
unnamed: UH6.20 (~CE), UN6.20 (~CE), UN7.3 (2)
unnamed: UJ6.20 (~CE), UN7.4 (3), UP6.20 (~CE)
unnamed: UP7.1, UP7.17 (Pin_1)
unnamed: UP7.2, UP7.18 (Pin_2)
unnamed: UP7.3, UP7.19 (Pin_3)
unnamed: UP7.4, UP7.20 (Pin_4)
unnamed: UP7.5, UP7.21 (Pin_5)
unnamed: UP7.6, UP7.22 (Pin_6)
unnamed: UP7.7, UP7.23 (Pin_7)
unnamed: UP7.9, UP7.25 (Pin_9)
unnamed: UP7.10, UP7.26 (Pin_10)
unnamed: UP7.11, UP7.27 (Pin_11)
unnamed: UP7.12, UP7.28 (Pin_12)
unnamed: UP7.13, UP7.29 (Pin_13)
unnamed: UP7.14, UP7.30 (Pin_14)
unnamed: UP7.15, UP7.31 (Pin_15)
unnamed: UR1.1, UR1.17 (Pin_1)
unnamed: UR1.2, UR1.18 (Pin_2)
unnamed: UR1.3, UR1.19 (Pin_3)
unnamed: UR1.4, UR1.20 (Pin_4)
unnamed: UR1.5, UR1.21 (Pin_5)
unnamed: UR1.6, UR1.22 (Pin_6)
unnamed: UR1.7, UR1.23 (Pin_7)
unnamed: UR1.9, UR1.25 (Pin_9)
unnamed: UR1.10, UR1.26 (Pin_10)
unnamed: UR1.11, UR1.27 (Pin_11)
unnamed: UR1.12, UR1.28 (Pin_12)
unnamed: UR1.13, UR1.29 (Pin_13)
unnamed: UR1.14, UR1.30 (Pin_14)
unnamed: UR1.15, UR1.31 (Pin_15)
unnamed: UR2.15 (C), US2.7, US2.10 (T)
unnamed: UP2.13, UR2.9 (~PE), US2.9 (~PE)
unnamed: UR3.15 (C), US3.7, US3.10 (T)
unnamed: UR7.1, UR7.17 (Pin_1)
unnamed: UR7.2, UR7.18 (Pin_2)
unnamed: UR7.3, UR7.19 (Pin_3)
unnamed: UR7.4, UR7.20 (Pin_4)
unnamed: UR7.5, UR7.21 (Pin_5)
unnamed: UR7.6, UR7.22 (Pin_6)
unnamed: UR7.7, UR7.23 (Pin_7)
unnamed: UR7.9, UR7.25 (Pin_9)
unnamed: UR7.10, UR7.26 (Pin_10)
unnamed: UR7.11, UR7.27 (Pin_11)
unnamed: UR7.12, UR7.28 (Pin_12)
unnamed: UR7.13, UR7.29 (Pin_13)
unnamed: UR7.14, UR7.30 (Pin_14)
unnamed: UR7.15, UR7.31 (Pin_15)
unnamed: US1.1, US1.17 (Pin_1)
unnamed: US1.2, US1.18 (Pin_2)
unnamed: US1.3, US1.19 (Pin_3)
unnamed: US1.4, US1.20 (Pin_4)
unnamed: US1.5, US1.21 (Pin_5)
unnamed: US1.6, US1.22 (Pin_6)
unnamed: US1.7, US1.23 (Pin_7)
unnamed: US1.9, US1.25 (Pin_9)
unnamed: US1.10, US1.26 (Pin_10)
unnamed: US1.11, US1.27 (Pin_11)
unnamed: US1.12, US1.28 (Pin_12)
unnamed: US1.13, US1.29 (Pin_13)
unnamed: US1.14, US1.30 (Pin_14)
unnamed: US1.15, US1.31 (Pin_15)
unnamed: UP2.11, UP2.12, US2.15 (C)
unnamed: UP2.8, UP2.9, US3.15 (C)
unnamed: UP2.10, US3.9 (~PE)
unnamed: US4.1, US4.17 (Pin_1)
unnamed: US4.2, US4.18 (Pin_2)
unnamed: US4.3, US4.19 (Pin_3)
unnamed: US4.4, US4.20 (Pin_4)
unnamed: US4.5, US4.21 (Pin_5)
unnamed: US4.6, US4.22 (Pin_6)
unnamed: US4.7, US4.23 (Pin_7)
unnamed: US4.9, US4.25 (Pin_9)
unnamed: US4.10, US4.26 (Pin_10)
unnamed: US4.11, US4.27 (Pin_11)
unnamed: US4.12, US4.28 (Pin_12)
unnamed: US4.13, US4.29 (Pin_13)
unnamed: US4.14, US4.30 (Pin_14)
unnamed: US4.15, US4.31 (Pin_15)
unnamed: US7.1, US7.17 (Pin_1)
unnamed: US7.2, US7.18 (Pin_2)
unnamed: US7.3, US7.19 (Pin_3)
unnamed: US7.4, US7.20 (Pin_4)
unnamed: US7.5, US7.21 (Pin_5)
unnamed: US7.6, US7.22 (Pin_6)
unnamed: US7.7, US7.23 (Pin_7)
unnamed: US7.9, US7.25 (Pin_9)
unnamed: US7.10, US7.26 (Pin_10)
unnamed: US7.11, US7.27 (Pin_11)
unnamed: US7.12, US7.28 (Pin_12)
unnamed: US7.13, US7.29 (Pin_13)
unnamed: US7.14, US7.30 (Pin_14)
unnamed: US7.15, US7.31 (Pin_15)
P: J2.P (Pin_35), R39.1, RM7.7 (R6)
P1: R32.1, UC9.3 (D0), UC9.4 (D1), UC9.5 (D2), UC9.6 (D3)
P2: R55.1, UA8.4 (K), UA8.10 (~R), UA8.11 (K), UA8.13 (~R), UC8.1 (~R), UC8.4 (~S), UC8.13 (~R)
P3: R56.1, UE1.1 (~MR), UE1.7, UE1.10 (T), UE2.1 (~MR), UF4.2, UF4.13, UH1.1 (~Mr)
P4: R57.1, UA5.3 (I1a), UA5.5 (I0b), UB5.1 (Mr), UC5.1 (Mr), UD4.1 (~Mr)
P5: R58.1, UM5.1 (~R), UM5.4 (~S), UM5.10 (~S), UM5.13 (~R), UN3.4 (~S), UN3.13 (~R)
P6: R59.1, UR2.1 (~MR), UR2.5 (D2), UR2.6 (D3), UR3.1 (~MR), UR3.9 (~PE), US2.1 (~MR), US2.3 (D0), US2.4 (D1), US2.5 (D2), US3.1 (~MR), US3.5 (D2)
R: J2.R (Pin_36), R38.1, RM7.8 (R7)
T: J2.T (Pin_38), R16.1, R17.1, R18.1
U: J2.U (Pin_39), R33.1, R34.1
V: J2.V (Pin_40), R37.1, RM7.9 (R8)
VCC: C2.1, C3.1, CP1.1, CP2.2, CP3.1, CP4.2, CP5.2, CP6.2, CP7.2, CP8.2, CP9.2, CP10.2, CP11.1, CP12.2, CP13.2, CP14.1, CP15.1, CP16.2, CP17.2, CP18.1, CP19.1, CP20.1, CP21.2, CP22.2, CP23.1, CP24.2, CP25.2, D9.1 (K), IR1.1 (S), J1.5, J1.6, J1.28, J2.18, Q6.3 (E), R5.1, R10.2, R11.1, R12.2, R19.2, R20.2, R30.2, R31.2, R32.2, R35.2, R53.1, R54.2, R55.2, R56.2, R57.2, R58.2, R59.2, RM1.1 (common), RM2.1 (common), RM3.1 (common), RM4.1 (common), RM5.1 (common), RM6.1 (common), RM7.1 (common), RM8.1 (common), UA1.16 (VCC), UA2.16 (VCC), UA3.16 (VCC), UA4.16 (VCC), UA5.16 (VCC), UA8.14 (VCC), UB1.16 (VCC), UB2.16 (VCC), UB3.16 (VCC), UB4.20 (VCC), UB5.16 (VCC), UB6.11 (VCC), UB8.16 (VCC), UC1.16 (VCC), UC2.16 (VCC), UC3.16 (VCC), UC4.14 (VCC), UC5.16 (VCC), UC8.14 (VCC), UC9.16 (VCC), UD1.16 (VCC), UD2.16 (VCC), UD3.5 (VCC), UD4.20 (VCC), UD6.28 (VCC), UD8.16 (VCC), UE1.16 (VCC), UE2.16 (VCC), UE3.14 (VCC), UE4.16 (VCC), UE5.21 (VPP), UE5.24 (VCC), UE6.21 (VPP), UE6.24 (VCC), UE8.16 (VCC), UF1.16 (VCC), UF2.16 (VCC), UF3.16 (VCC), UF4.14 (VCC), UF5.21 (VPP), UF5.24 (VCC), UF6.21 (VPP), UF6.24 (VCC), UF7.16 (VCC), UF8.16 (VCC), UH1.16 (VCC), UH2.14 (VCC), UH3.16 (VCC), UH4.20 (VCC), UH5.21 (VPP), UH5.24 (VCC), UH6.21 (VPP), UH6.24 (VCC), UH7.14 (VCC), UH8.16 (VCC), UH41.20 (VCC), UJ5.21 (VPP), UJ5.24 (VCC), UJ6.21 (VPP), UJ6.24 (VCC), UJ7.16 (VCC), UK1.16 (VCC), UK2.16 (VCC), UK3.16 (VCC), UK4.18 (VCC), UK6.21 (VPP), UK6.24 (VCC), UK7.16 (Vdd), UK8.16 (VCC), UL1.16 (VCC), UL2.16 (VCC), UL3.16 (VCC), UL4.18 (VCC), UL5.16 (VCC), UL7.14 (VCC), UM1.16 (VCC), UM2.20 (VCC), UM3.16 (VCC), UM4.18 (VCC), UM5.14 (VCC), UM6.21 (VPP), UM6.24 (VCC), UM7.16 (VCC), UN1.14 (VDD), UN3.14 (VCC), UN4.18 (VCC), UN5.14 (VCC), UN6.21 (VPP), UN6.24 (VCC), UN7.16 (VCC), UP2.14 (VCC), UP3.14 (VCC), UP4.18 (VCC), UP6.21 (VPP), UP6.24 (VCC), UP7.16, UP7.32 (Pin_16), UR1.16, UR1.32 (Pin_16), UR2.16 (VCC), UR3.16 (VCC), UR4.18 (VCC), UR6.16 (VCC), UR7.16, UR7.32 (Pin_16), US1.16, US1.32 (Pin_16), US2.16 (VCC), US3.16 (VCC), US4.16, US4.32 (Pin_16), US5.28 (VCC), US6.16 (VCC), US7.16, US7.32 (Pin_16)

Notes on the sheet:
Red
HEAT SINK
1N-4066
Credit
Down
Right
12VAC
7V C.T.
+7.5VDC
Table
12V C.T.
Left
Note: Use 2532 ROMS at 5E, 5F or use 2716 ROMS at 5E-5J
+5V
Coin 1
Test
Start 1
Note: Use UC3 or UD3
Blue
Coin 2
* NOTE: Substitute Z-80 Sync Buss Controller A082-91383- 8000
~{RESET}
Start 2
Green
7VAC
Speaker
Cocktail 2nd Player
Composite Sync
*** Note: Custom IC Substitute V-RAM Addresser A082-91384-8000
Coin Counter
Had to break this out (pullup)

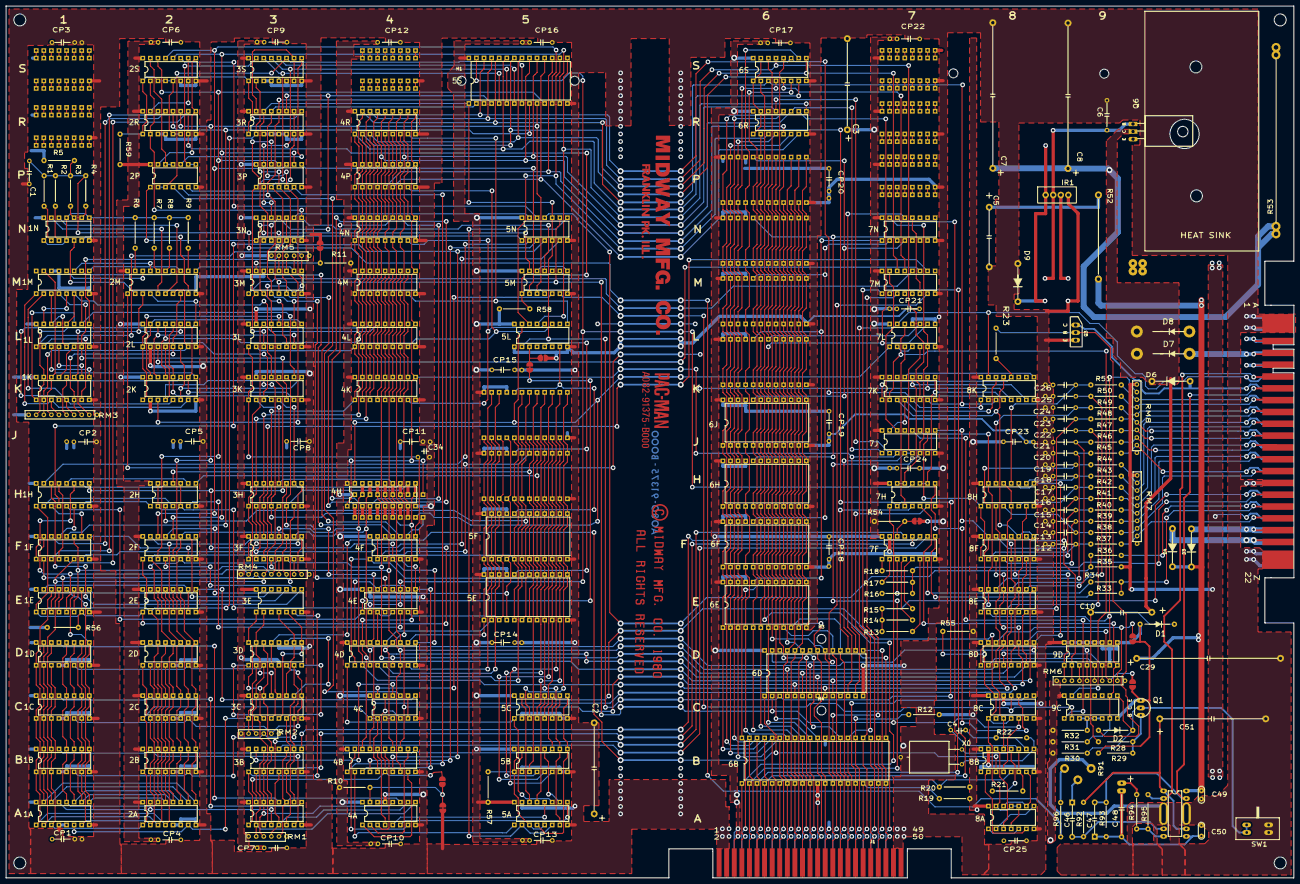
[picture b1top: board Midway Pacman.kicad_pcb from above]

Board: 2 copper layers, 431.5 x 292.1 mm, 259 parts (0 on the bottom side), 478 nets.
